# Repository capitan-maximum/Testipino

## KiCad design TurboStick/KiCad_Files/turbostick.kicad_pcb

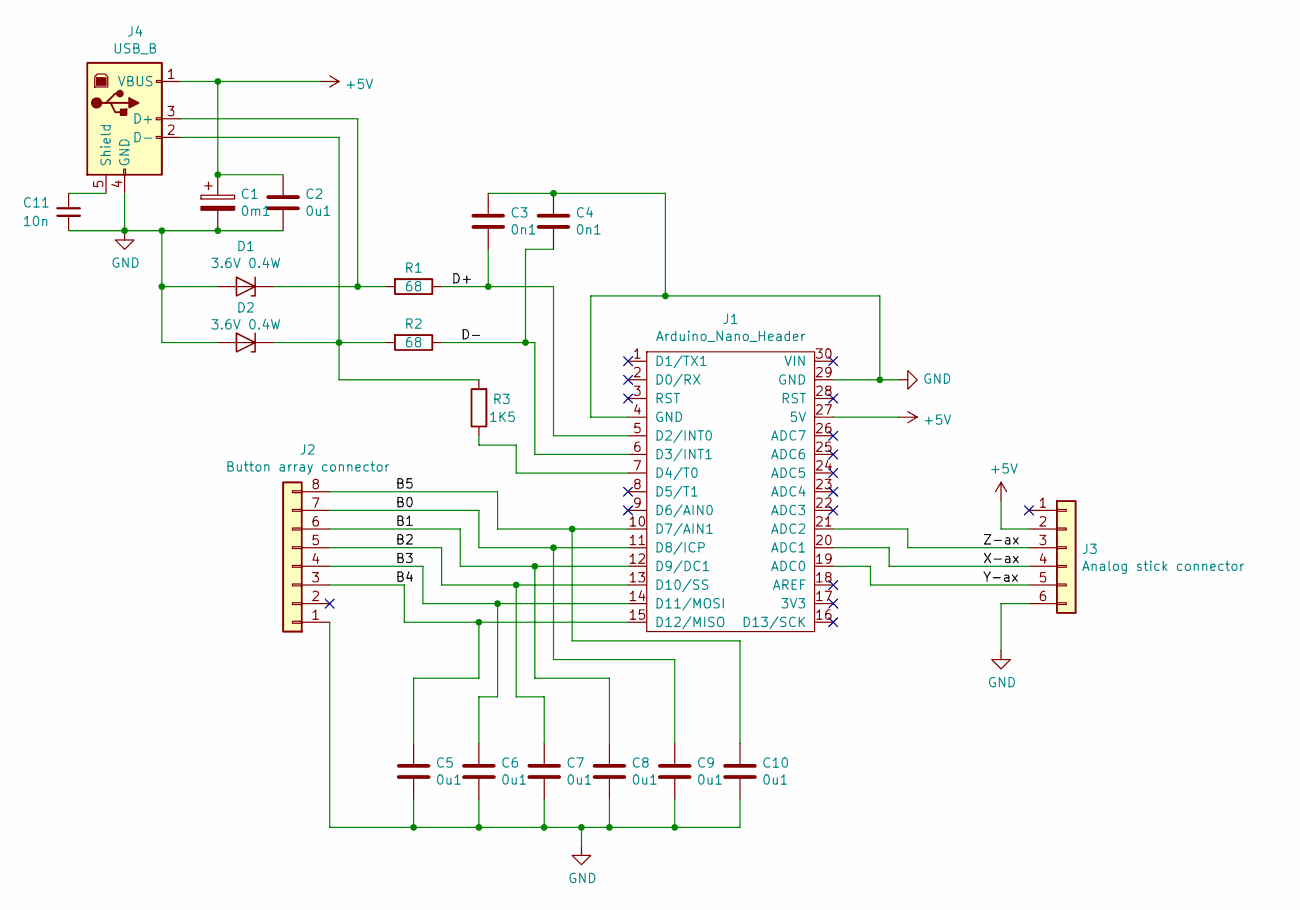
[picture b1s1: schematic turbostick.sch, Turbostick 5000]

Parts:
C1: 0m1; CP_Radial_D5.0mm_P2.50mm
C2, C5, C6, C7, C8, C9, C10: 0u1; C_Disc_D6.0mm_W2.5mm_P5.00mm
C3, C4: 0n1; C_Disc_D6.0mm_W2.5mm_P5.00mm
C11: 10n; C_Rect_L11.0mm_W3.4mm_P10.00mm_MKT
D1, D2: 3.6V 0.4W; D_A-405_P7.62mm_Horizontal
J1: Arduino_Nano_Header; Arduino_Nano
J2: Button array connector; PinHeader_1x08_P2.54mm_Vertical
J3: Analog stick connector; PinHeader_1x06_P2.54mm_Vertical
J4: USB_B; USB_B_OST_USB-B1HSxx_Horizontal
R1, R2: 68; R_Axial_DIN0207_L6.3mm_D2.5mm_P7.62mm_Horizontal
R3: 1K5; R_Axial_DIN0207_L6.3mm_D2.5mm_P7.62mm_Horizontal

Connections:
+5V: C1.1, C2.1, J1.27 (5V), J3.2, J4.1 (VBUS)
/B0: C9.1, J1.11 (D8/ICP), J2.7
/B1: C8.1, J1.12 (D9/DC1), J2.6
/B2: C7.1, J1.13 (D10/SS), J2.5
/B3: C6.1, J1.14 (D11/MOSI), J2.4
/B4: C5.1, J1.15 (D12/MISO), J2.3
/B5: C10.1, J1.10 (D7/AIN1), J2.8
/D+: C3.2, J1.5 (D2/INT0), R1.1
/D-: C4.2, J1.6 (D3/INT1), R2.1
/X-ax: J1.20 (ADC1), J3.4
/Y-ax: J1.19 (ADC0), J3.5
/Z-ax: J1.21 (ADC2), J3.3
GND: C1.2, C2.2, C3.1, C4.1, C5.2, C6.2, C7.2, C8.2, C9.2, C10.2, C11.2, D1.2 (A), D2.2 (A), J1.4 (GND), J1.29 (GND), J2.1, J3.6, J4.4 (GND)
unnamed: C11.1, J4.5 (Shield)
unnamed: D1.1 (K), J4.3 (D+), R1.2
unnamed: D2.1 (K), J4.2 (D-), R2.2, R3.2
unnamed: J1.7 (D4/T0), R3.1

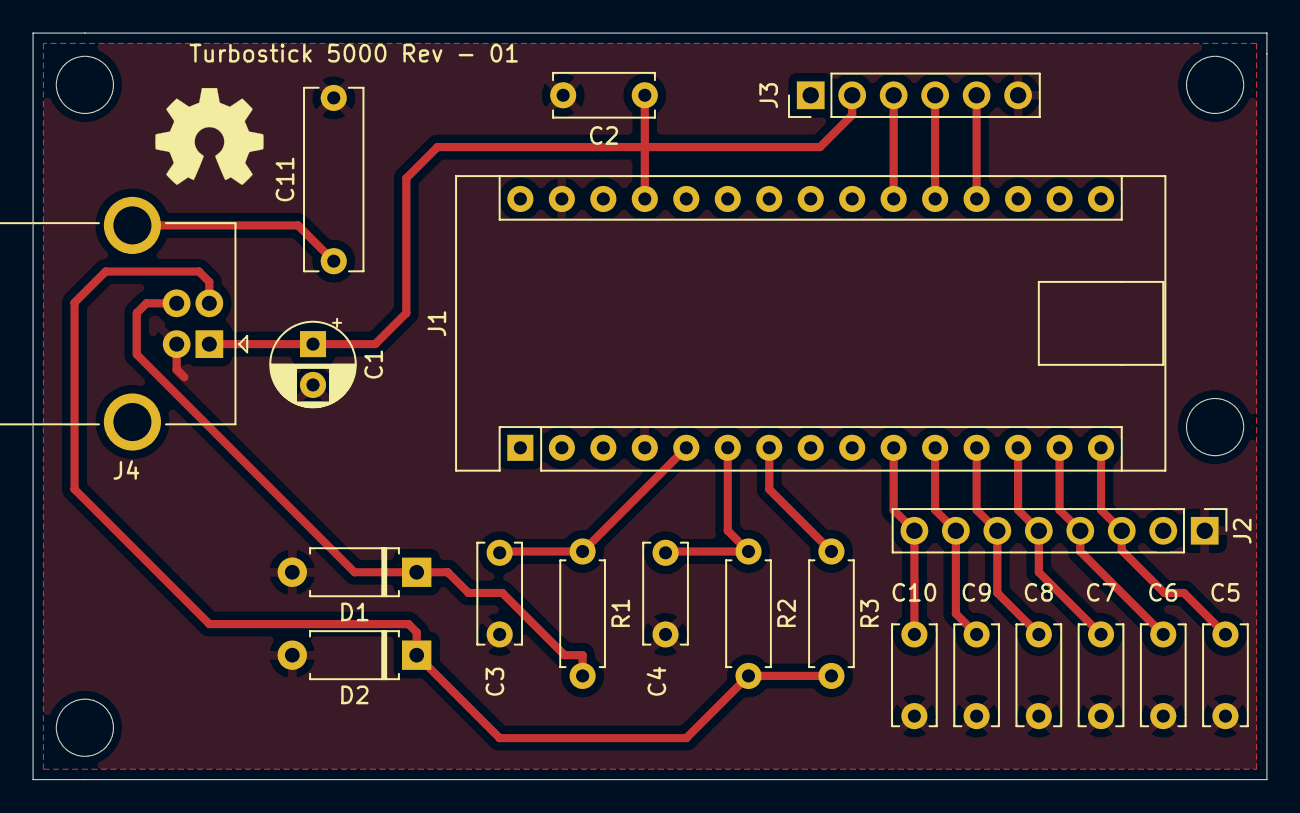
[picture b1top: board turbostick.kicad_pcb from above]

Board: 2 copper layers, 75.6 x 45.7 mm, 20 parts (0 on the bottom side), 17 nets.

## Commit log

2019-06-13 TurboStick
    Analog 3-axis USB-joystick using Arduino Nano
2019-06-13 Include .lib files in KiCad
2019-06-13 Buutti Oy:n esitehtävä
